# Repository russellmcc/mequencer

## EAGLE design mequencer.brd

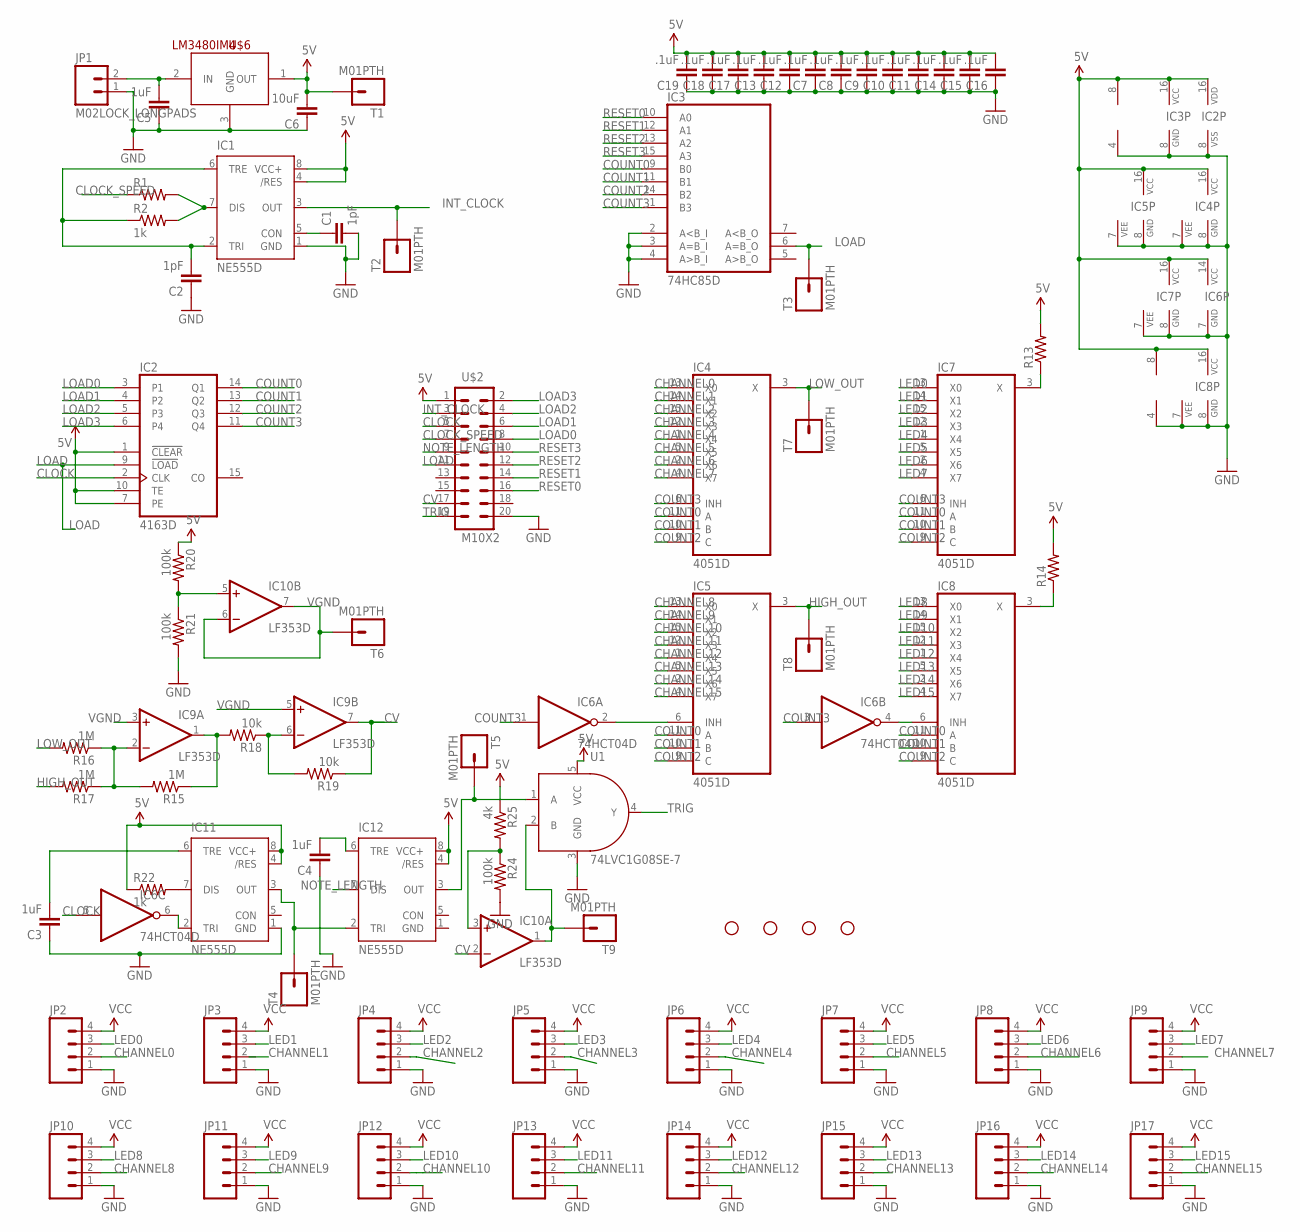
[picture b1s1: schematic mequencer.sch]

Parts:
C1, C2: 1pF; 0603-CAP
C3, C4, C5: 1uF; 0603-CAP
C6: 10uF; 0603-CAP
C7, C8, C9, C10, C11, C12, C13, C14, C15, C16, C17, C18, C19: .1uF; 0603-CAP
IC1, IC11, IC12: NE555D; SO08
IC2: 4163D; SO16
IC3: 74HC85D; SO16
IC4, IC5, IC7, IC8: 4051D; SO16
IC6: 74HCT04D; SO14
IC9, IC10: LF353D; SO08
JP1: M02LOCK_LONGPADS; 1X02_LOCK_LONGPADS
JP2, JP3, JP4, JP5, JP6, JP7, JP8, JP9, JP10, JP11, JP12, JP13, JP14, JP15, JP16, JP17: M04JST-PTH; JST-4-PTH
R1, R13, R14: RESISTOR0603; 0603-RES
R2, R22: 1k; 0603-RES
R15, R16, R17: 1M; 0603-RES
R18, R19: 10k; 0603-RES
R20, R21, R24: 100k; 0603-RES
R25: 4k; 0603-RES
STANDOFF1, STANDOFF2, STANDOFF3, STANDOFF4: STAND-OFF
T1, T2, T3, T4, T5, T6, T7, T8, T9: M01PTH; 1X01
U1: 74LVC1G08SE-7; SOT353
U$2: M10X2; 2X10
U$6: LM3480IM4; SOT23-3

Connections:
5V: C6.2, C7.2, C8.2, C9.2, C10.2, C11.2, C12.2, C13.2, C14.2, C15.2, C16.2, C17.2, C18.2, C19.2, IC1.4 (/RES), IC1.8 (VCC+), IC2.1 (!CLEAR), IC2.7 (PE), IC2.10 (TE), IC2.16 (VDD), IC3.16 (VCC), IC4.16 (VCC), IC5.16 (VCC), IC6.14 (VCC), IC7.16 (VCC), IC8.16 (VCC), IC9.8 (V+), IC10.8 (V+), IC11.4 (/RES), IC11.8 (VCC+), IC12.4 (/RES), IC12.8 (VCC+), R13.2, R14.2, R20.1, R22.1, R25.1, T1.1, U1.5 (VCC), U$2.1, U$6.1 (OUT)
CHANNEL0: IC4.13 (X0), JP2.2
CHANNEL1: IC4.14 (X1)
CHANNEL2: IC4.15 (X2), JP4.2
CHANNEL3: IC4.12 (X3), JP5.2
CHANNEL4: IC4.1 (X4), JP6.2
CHANNEL5: IC4.5 (X5), JP7.2
CHANNEL6: IC4.2 (X6), JP8.2
CHANNEL7: IC4.4 (X7), JP9.2
CHANNEL8: IC5.13 (X0), JP10.2
CHANNEL9: IC5.14 (X1), JP11.2
CHANNEL10: IC5.15 (X2), JP12.2
CHANNEL11: IC5.12 (X3), JP13.2
CHANNEL12: IC5.1 (X4), JP14.2
CHANNEL13: IC5.5 (X5), JP15.2
CHANNEL14: IC5.2 (X6), JP16.2
CHANNEL15: IC5.4 (X7), JP17.2
CLOCK: IC2.2 (CLK), IC6.5 (I), U$2.5
CLOCK_SPEED: R1.1, U$2.7
COUNT0: IC2.14 (Q1), IC3.9 (B0), IC4.11 (A), IC5.11 (A), IC7.11 (A), IC8.11 (A)
COUNT1: IC2.13 (Q2), IC3.11 (B1), IC4.10 (B), IC5.10 (B), IC7.10 (B), IC8.10 (B)
COUNT2: IC2.12 (Q3), IC3.14 (B2), IC4.9 (C), IC5.9 (C), IC7.9 (C), IC8.9 (C)
COUNT3: IC2.11 (Q4), IC3.1 (B3), IC4.6 (INH), IC6.1 (I), IC6.3 (I), IC7.6 (INH)
CV: IC9.7 (OUT), IC10.2 (-IN), R19.1, U$2.17
GND: C1.2, C2.1, C3.1, C4.1, C5.1, C6.1, C7.1, C8.1, C9.1, C10.1, C11.1, C12.1, C13.1, C14.1, C15.1, C16.1, C17.1, C18.1, C19.1, IC1.1 (GND), IC2.8 (VSS), IC3.2 (A<B_I), IC3.3 (A=B_I), IC3.4 (A>B_I), IC3.8 (GND), IC4.7 (VEE), IC4.8 (GND), IC5.7 (VEE), IC5.8 (GND), IC6.7 (GND), IC7.7 (VEE), IC7.8 (GND), IC8.7 (VEE), IC8.8 (GND), IC9.4 (V-), IC10.4 (V-), IC11.1 (GND), IC12.1 (GND), JP1.1, JP2.1, JP3.1, JP4.1, JP5.1, JP6.1, JP7.1, JP8.1, JP9.1, JP10.1, JP11.1, JP12.1, JP13.1, JP14.1, JP15.1, JP16.1, JP17.1, R21.2, R24.2, U1.3 (GND), U$2.20, U$6.3 (GND)
HIGH_OUT: IC5.3 (X), R17.2, T8.1
INT_CLOCK: IC1.3 (OUT), T2.1, U$2.3
LED0: IC7.13 (X0), JP2.3
LED1: IC7.14 (X1), JP3.3
LED2: IC7.15 (X2), JP4.3
LED3: IC7.12 (X3), JP5.3
LED4: IC7.1 (X4), JP6.3
LED5: IC7.5 (X5), JP7.3
LED6: IC7.2 (X6), JP8.3
LED7: IC7.4 (X7), JP9.3
LED8: IC8.13 (X0), JP10.3
LED9: IC8.14 (X1), JP11.3
LED10: IC8.15 (X2), JP12.3
LED11: IC8.12 (X3), JP13.3
LED12: IC8.1 (X4), JP14.3
LED13: IC8.5 (X5), JP15.3
LED14: IC8.2 (X6), JP16.3
LED15: IC8.4 (X7), JP17.3
LOAD: IC2.9 (!LOAD), IC3.6 (A=B_O), T3.1, U$2.11
LOAD0: IC2.3 (P1), U$2.8
LOAD1: IC2.4 (P2), U$2.6
LOAD2: IC2.5 (P3), U$2.4
LOAD3: IC2.6 (P4), U$2.2
LOW_OUT: IC4.3 (X), R16.2, T7.1
unnamed: C1.1, IC1.5 (CON)
unnamed: IC1.7 (DIS), R1.2, R2.2
unnamed: C2.2, IC1.2 (TRI), IC1.6 (TRE), R2.1
unnamed: IC5.6 (INH), IC6.2 (O)
unnamed: IC6.4 (O), IC8.6 (INH)
unnamed: IC7.3 (X), R13.1
unnamed: IC9.1 (OUT), R15.1, R18.2
unnamed: IC9.2 (-IN), R15.2, R16.1, R17.1
unnamed: IC9.6 (-IN), R18.1, R19.2
unnamed: IC10.5 (+IN), R20.2, R21.1
unnamed: IC11.7 (DIS), R22.2
unnamed: C3.2, IC11.6 (TRE)
unnamed: IC8.3 (X), R14.1
unnamed: IC6.6 (O), IC11.2 (TRI)
unnamed: C4.2, IC12.6 (TRE)
unnamed: IC10.1 (OUT), T9.1, U1.2 (B)
unnamed: IC11.3 (OUT), IC12.2 (TRI), T4.1
unnamed: IC10.3 (+IN), R24.1, R25.2
unnamed: IC12.3 (OUT), T5.1, U1.1 (A)
unnamed: C5.2, JP1.2, U$6.2 (IN)
NOTE_LENGTH: IC12.7 (DIS), U$2.9
RESET0: IC3.10 (A0), U$2.16
RESET1: IC3.12 (A1), U$2.14
RESET2: IC3.13 (A2), U$2.12
RESET3: IC3.15 (A3), U$2.10
TRIG: U1.4 (Y), U$2.19
VCC: JP2.4, JP3.4, JP4.4, JP5.4, JP6.4, JP7.4, JP8.4, JP9.4, JP10.4, JP11.4, JP12.4, JP13.4, JP14.4, JP15.4, JP16.4, JP17.4
VGND: IC9.3 (+IN), IC9.5 (+IN), IC10.6 (-IN), IC10.7 (OUT), T6.1

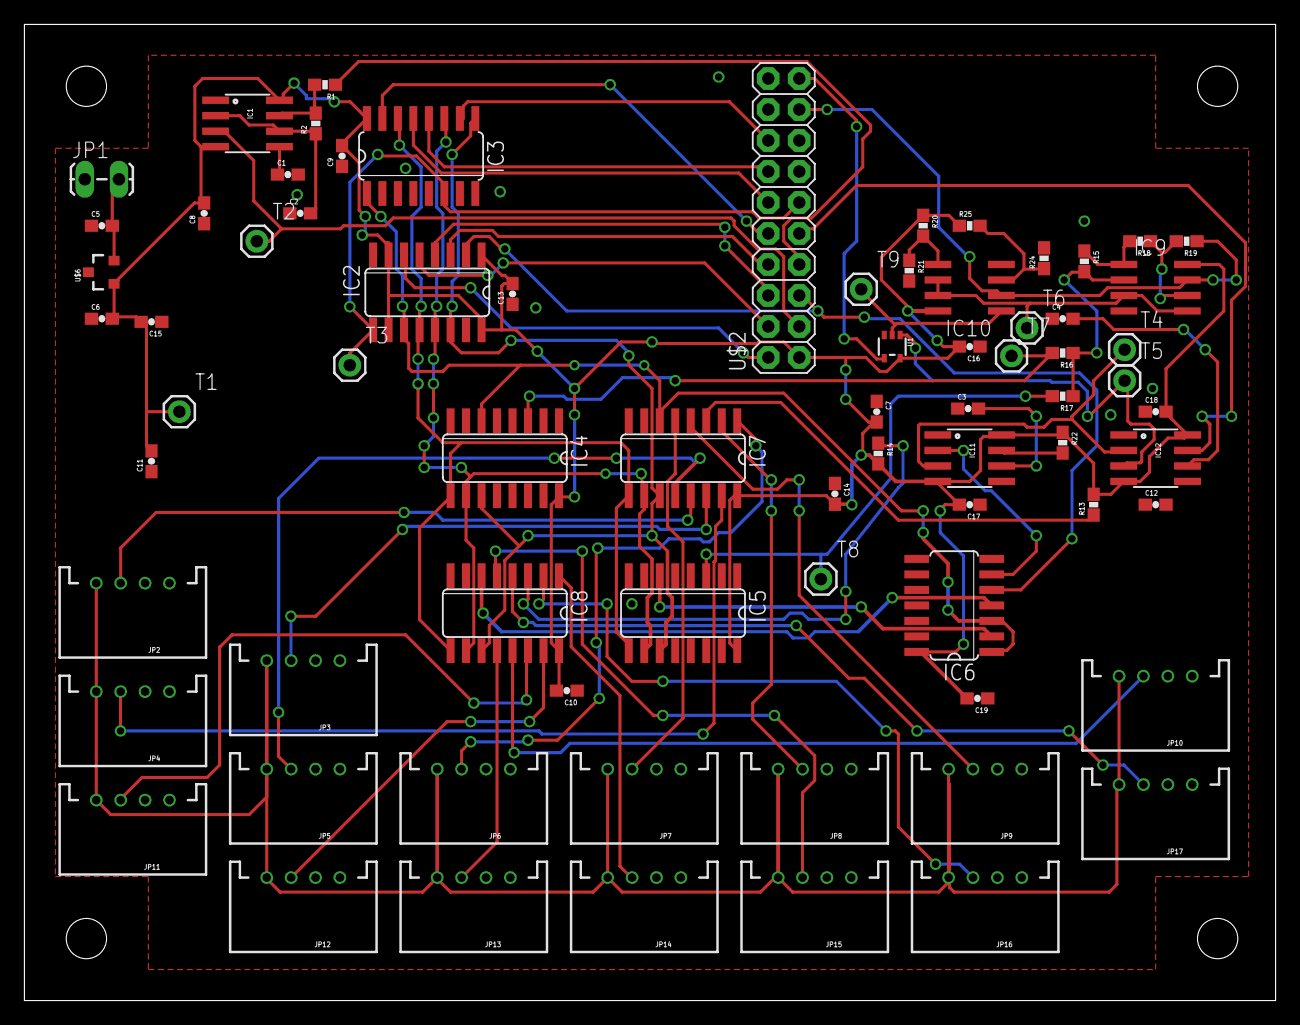
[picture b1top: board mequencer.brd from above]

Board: 2 copper layers, 102.5 x 80.0 mm, 78 parts (0 on the bottom side), 76 nets.

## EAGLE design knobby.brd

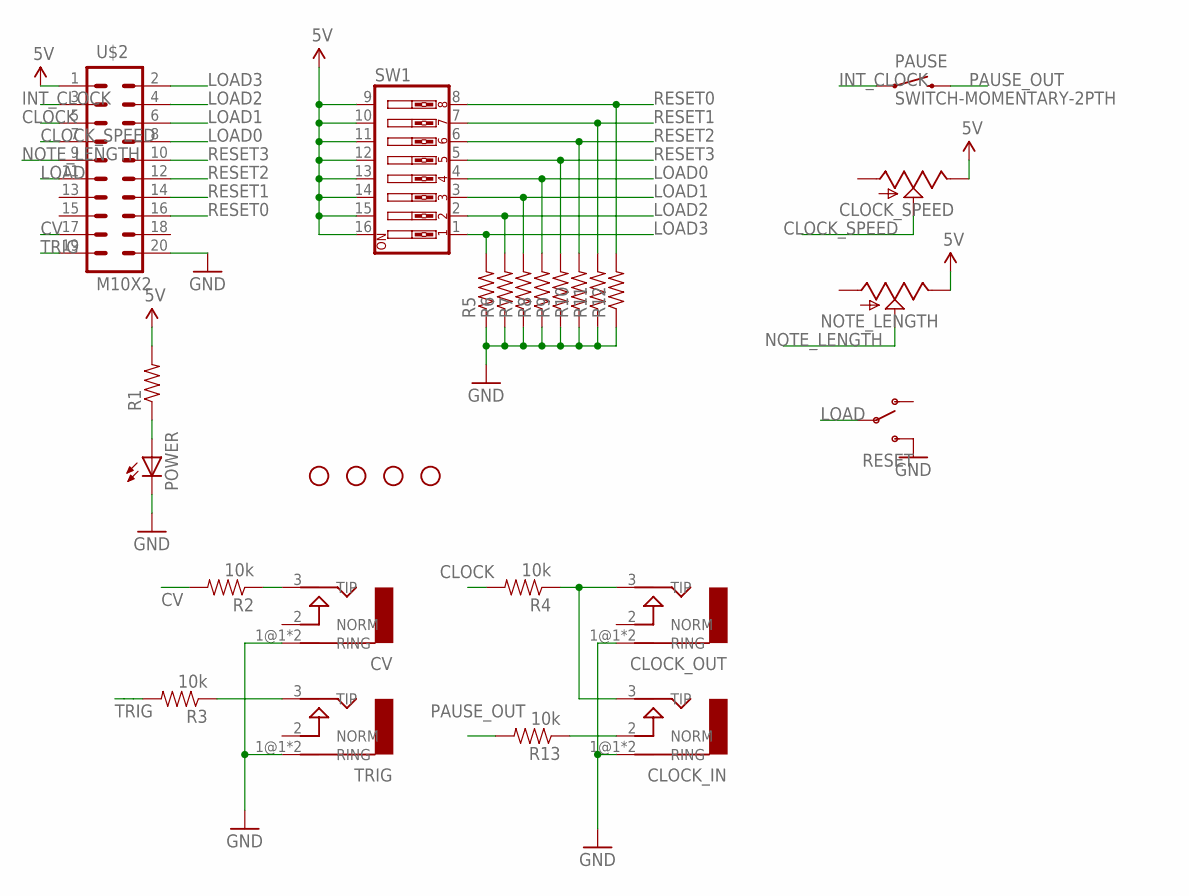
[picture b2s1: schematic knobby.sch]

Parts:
CLOCK_IN: AUDIO-JACKERTHENVAR; ERTHENVAR-JACK
CLOCK_OUT: AUDIO-JACKERTHENVAR; ERTHENVAR-JACK
CLOCK_SPEED: SPARKFUN_POTPDB12; SPARKFUN_PDB12
CV: AUDIO-JACKERTHENVAR; ERTHENVAR-JACK
NOTE_LENGTH: SPARKFUN_POTPDB12; SPARKFUN_PDB12
PAUSE: SWITCH-MOMENTARY-2PTH; TACTILE-PTH
POWER: LED3MM
R1, R5, R6, R7, R8, R9, R10, R11, R12: RESISTOR0603; 0603-RES
R2, R3, R4, R13: 10k; 0603-RES
RESET: SWITCH-SPDTPTH; SWITCH-SPDT
STANDOFF1, STANDOFF2, STANDOFF3, STANDOFF4: STAND-OFF
SW1: SW_DIP-8; DIPSWITCH-08
TRIG: AUDIO-JACKERTHENVAR; ERTHENVAR-JACK
U$2: M10X2; 2X10

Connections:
5V: CLOCK_SPEED.3 (E), NOTE_LENGTH.3 (E), R1.2, SW1.9, SW1.10, SW1.11, SW1.12, SW1.13, SW1.14, SW1.15, SW1.16, U$2.1
CLOCK: R4.2, U$2.5
CLOCK_SPEED: CLOCK_SPEED.2 (S), U$2.7
CV: R2.2, U$2.17
GND: CLOCK_IN.1@1 (RING), CLOCK_IN.1@2 (RING), CLOCK_OUT.1@1 (RING), CLOCK_OUT.1@2 (RING), CV.1@1 (RING), CV.1@2 (RING), POWER.K (C), R5.1, R6.1, R7.1, R8.1, R9.1, R10.1, R11.1, R12.1, RESET.3 (S), TRIG.1@1 (RING), TRIG.1@2 (RING), U$2.20
INT_CLOCK: PAUSE.1, U$2.3
LOAD: RESET.2, U$2.11
LOAD0: R8.2, SW1.4, U$2.8
LOAD1: R7.2, SW1.3, U$2.6
LOAD2: R6.2, SW1.2, U$2.4
LOAD3: R5.2, SW1.1, U$2.2
unnamed: POWER.A, R1.1
unnamed: CV.3 (TIP), R2.1
unnamed: R3.1, TRIG.3 (TIP)
unnamed: CLOCK_IN.3 (TIP), CLOCK_OUT.3 (TIP), R4.1
unnamed: CLOCK_IN.2 (NORM), R13.1
NOTE_LENGTH: NOTE_LENGTH.2 (S), U$2.9
PAUSE_OUT: PAUSE.3 (2), R13.2
RESET0: R12.2, SW1.8, U$2.16
RESET1: R11.2, SW1.7, U$2.14
RESET2: R10.2, SW1.6, U$2.12
RESET3: R9.2, SW1.5, U$2.10
TRIG: R3.2, U$2.19

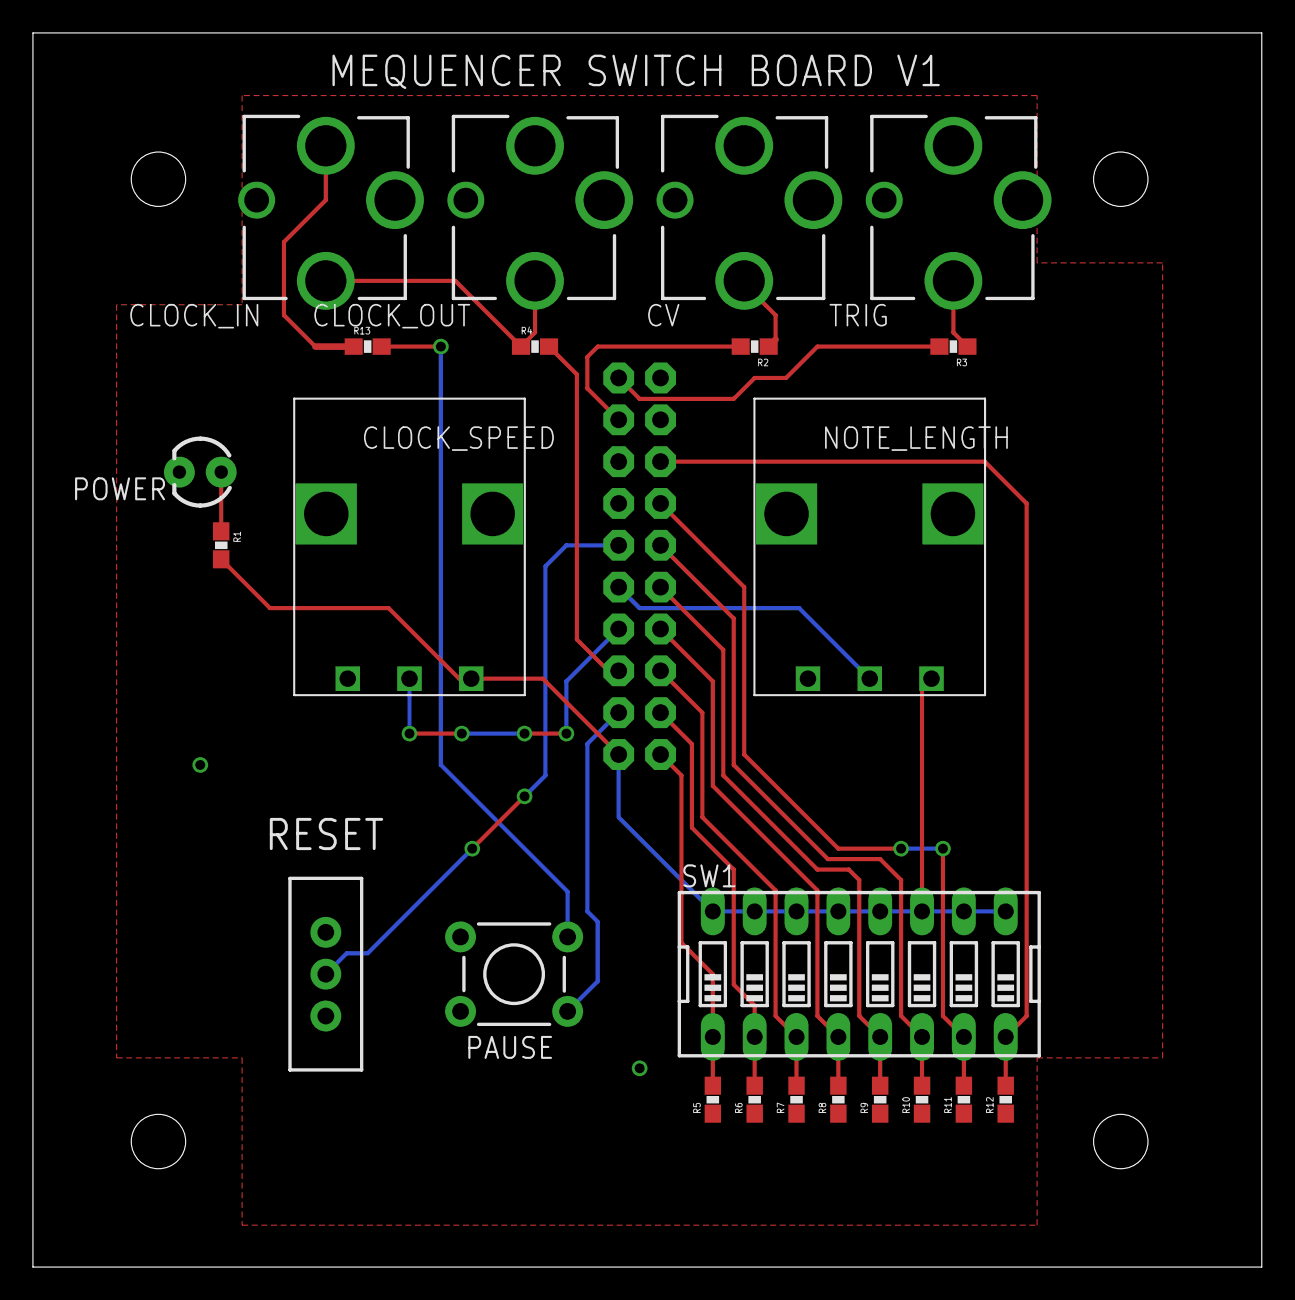
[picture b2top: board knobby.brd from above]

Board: 2 copper layers, 74.6 x 74.9 mm, 28 parts (1 on the bottom side), 23 nets.

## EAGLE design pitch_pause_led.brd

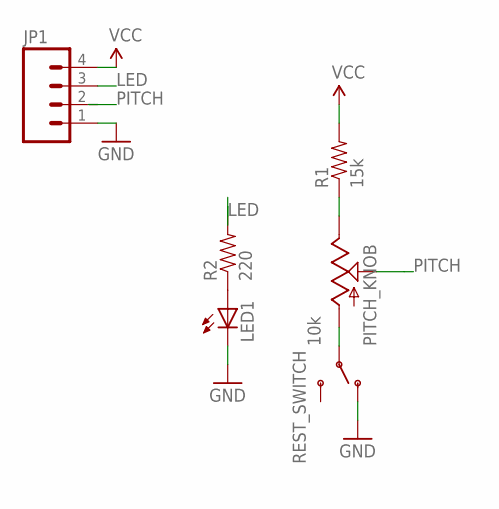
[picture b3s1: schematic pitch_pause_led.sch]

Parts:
JP1: M04JST-PTH; JST-4-PTH
LED1: LED-3MM-NO_SILK; LED3MM-NS
PITCH_KNOB: 10k; SPARKFUN_PDB12
R1: 15k; AXIAL-0.3
R2: 220; AXIAL-0.3
REST_SWITCH: SWITCH-SPDTPTH_LOCK; SWITCH-SPDT_LOCK.007S

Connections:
GND: JP1.1, LED1.K (C), REST_SWITCH.1 (O)
LED: JP1.3, R2.P$2 (2)
unnamed: PITCH_KNOB.1 (A), REST_SWITCH.2
unnamed: PITCH_KNOB.3 (E), R1.P$1 (1)
unnamed: LED1.A, R2.P$1 (1)
PITCH: PITCH_KNOB.2 (S)
VCC: JP1.4, R1.P$2 (2)

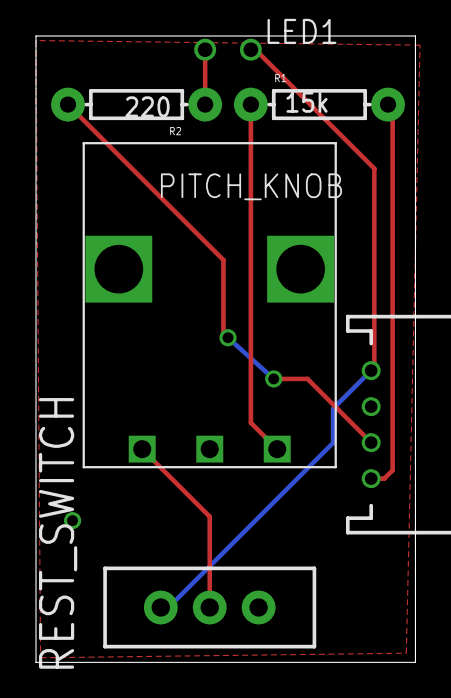
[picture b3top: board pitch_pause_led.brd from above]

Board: 2 copper layers, 21.1 x 34.8 mm, 6 parts (0 on the bottom side), 6 nets.

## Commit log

2013-11-02 initial
2013-11-09 55555555555555555
2013-11-09 Board1 headers and power and stuff. schematic done?
2013-11-09 Added knobby expansion board
2013-11-13 Added LEDS to knobby board
2013-11-16 16 pots
2013-11-16 knobby brd
2013-11-20 mini boards
2013-11-28 Knobby board layed out with 4 jacks
2013-12-08 through hole led on mini boards
2013-12-16 Moving shit around
2013-12-16 Moving shit around more
2014-01-20 stuff
2014-02-15 Muxxes all wired up
2014-03-06 main board all wired up
2014-03-22 changed some 1ks to 100ks to draw less current
2014-03-22 bumped the resistance values in the CV summer so that the resistance in note pot won't affect the note's CV when it is in rest mode
2014-05-17 test points and jack resistors

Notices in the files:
parts and their libraries:
SparkFun-Connectors: Licensing: CC v3.0 Share-Alike You are welcome to use this library for commercial purposes.
